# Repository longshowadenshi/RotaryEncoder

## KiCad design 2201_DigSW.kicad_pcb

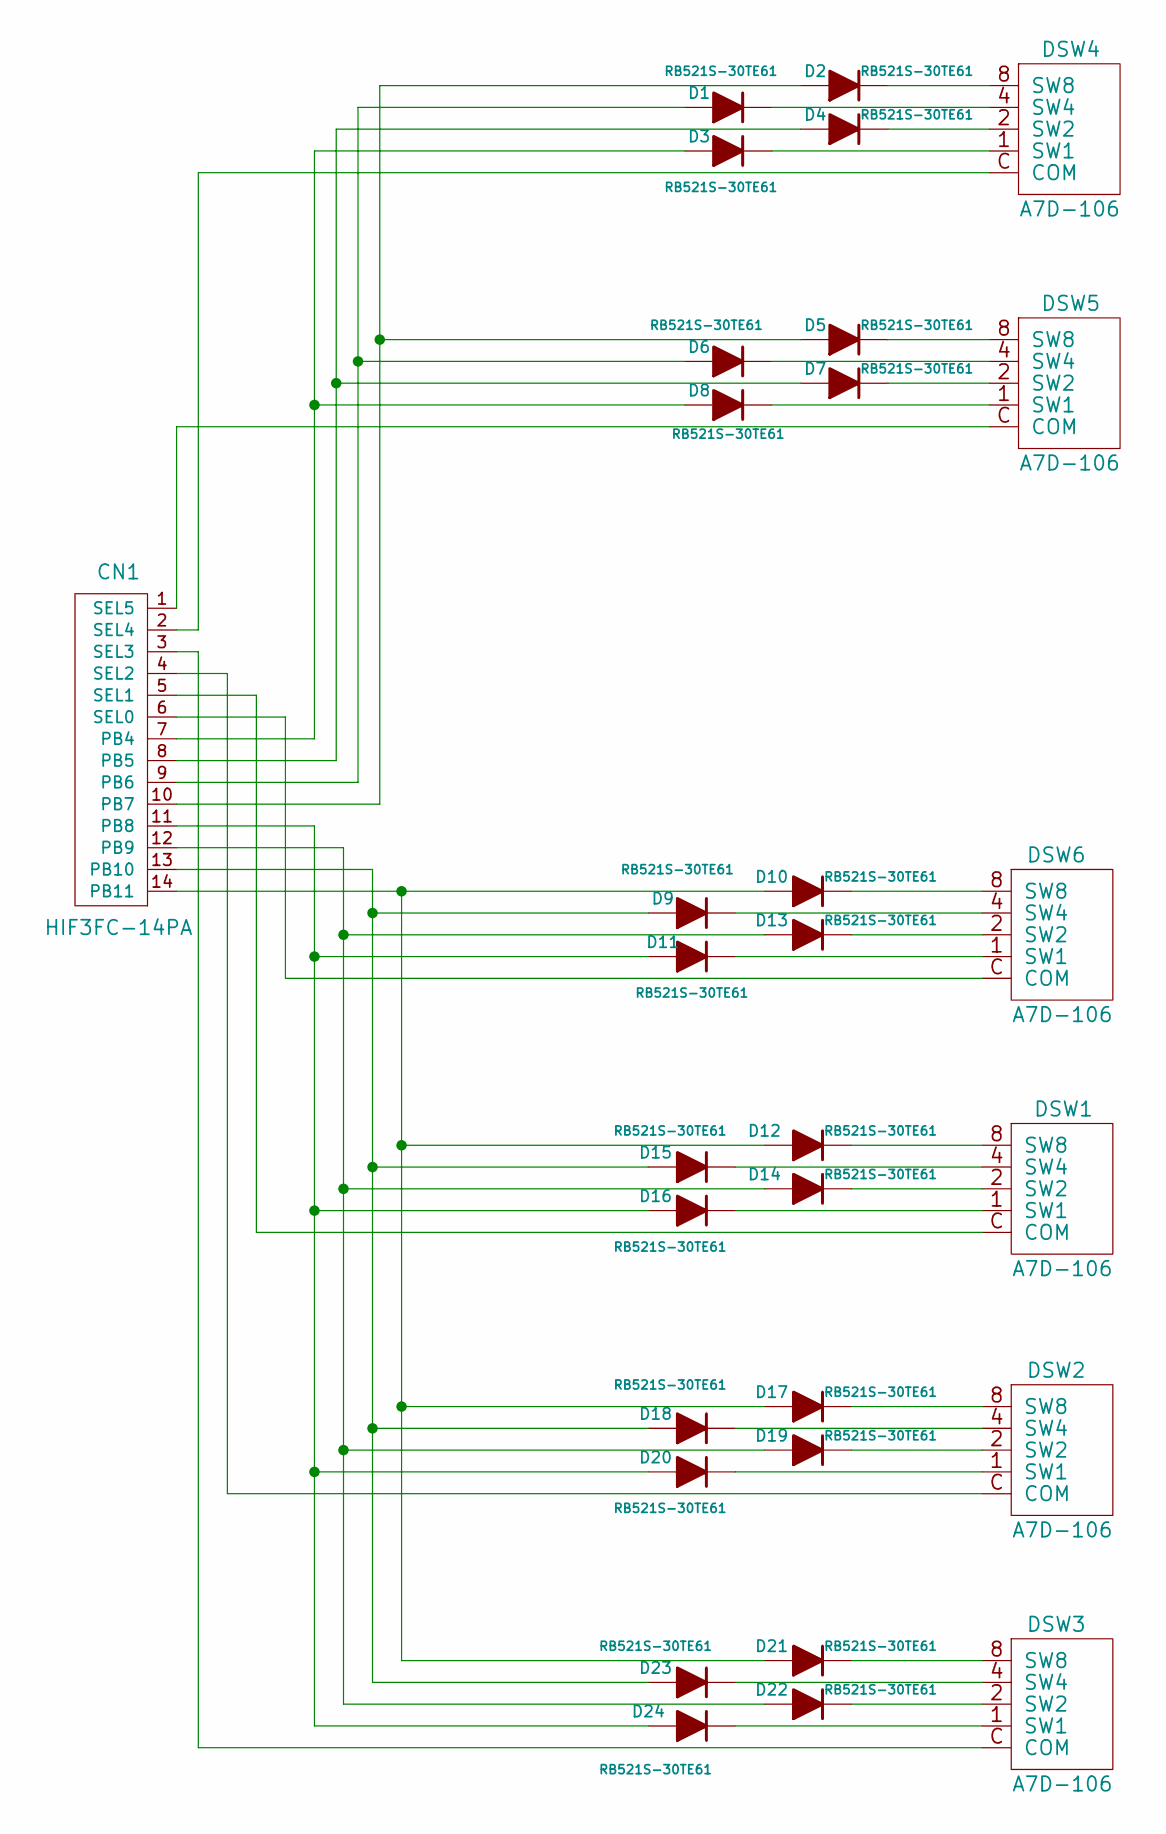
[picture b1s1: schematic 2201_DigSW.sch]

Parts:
CN1: HIF3FC-14PA; HIF3FC
D1, D2, D3, D4, D5, D6, D7, D8, D9, D10, D11, D12, D13, D14, D15, D16, D17, D18, D19, D20, D21, D22, D23, D24: RB521S-30TE61; 1SS355
DSW1, DSW3, DSW5: A7D-106; A7D-106-R
DSW2, DSW4, DSW6: A7D-106; A7D-106-L

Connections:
unnamed: CN1.1 (SEL5), DSW5.C (COM)
unnamed: CN1.2 (SEL4), DSW4.C (COM)
unnamed: CN1.3 (SEL3), DSW3.C (COM)
unnamed: CN1.4 (SEL2), DSW2.C (COM)
unnamed: CN1.5 (SEL1), DSW1.C (COM)
unnamed: CN1.6 (SEL0), DSW6.C (COM)
unnamed: CN1.7 (PB4), D3.1, D8.1
unnamed: CN1.8 (PB5), D4.1, D7.1
unnamed: CN1.9 (PB6), D1.1, D6.1
unnamed: CN1.10 (PB7), D2.1, D5.1
unnamed: CN1.11 (PB8), D11.1, D16.1, D20.1, D24.1
unnamed: CN1.12 (PB9), D13.1, D14.1, D19.1, D22.1
unnamed: CN1.13 (PB10), D9.1, D15.1, D18.1, D23.1
unnamed: CN1.14 (PB11), D10.1, D12.1, D17.1, D21.1
unnamed: D1.2, DSW4.4 (SW4)
unnamed: D2.2, DSW4.8 (SW8)
unnamed: D3.2, DSW4.1 (SW1)
unnamed: D4.2, DSW4.2 (SW2)
unnamed: D5.2, DSW5.8 (SW8)
unnamed: D6.2, DSW5.4 (SW4)
unnamed: D7.2, DSW5.2 (SW2)
unnamed: D8.2, DSW5.1 (SW1)
unnamed: D9.2, DSW6.4 (SW4)
unnamed: D10.2, DSW6.8 (SW8)
unnamed: D11.2, DSW6.1 (SW1)
unnamed: D12.2, DSW1.8 (SW8)
unnamed: D13.2, DSW6.2 (SW2)
unnamed: D14.2, DSW1.2 (SW2)
unnamed: D15.2, DSW1.4 (SW4)
unnamed: D16.2, DSW1.1 (SW1)
unnamed: D17.2, DSW2.8 (SW8)
unnamed: D18.2, DSW2.4 (SW4)
unnamed: D19.2, DSW2.2 (SW2)
unnamed: D20.2, DSW2.1 (SW1)
unnamed: D21.2, DSW3.8 (SW8)
unnamed: D22.2, DSW3.2 (SW2)
unnamed: D23.2, DSW3.4 (SW4)
unnamed: D24.2, DSW3.1 (SW1)

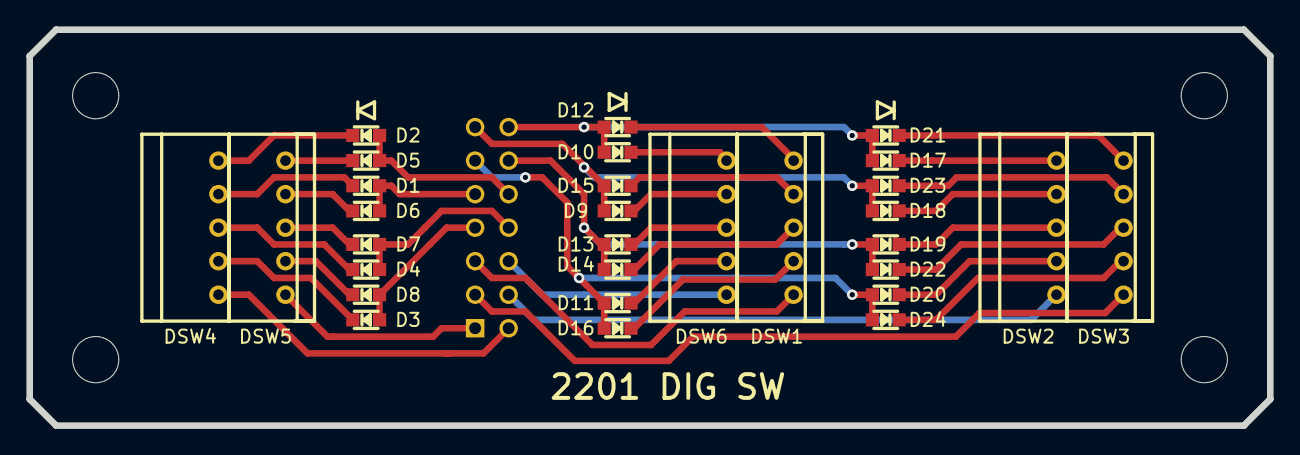
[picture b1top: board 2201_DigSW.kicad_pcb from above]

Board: 2 copper layers, 94.0 x 30.0 mm, 31 parts (1 on the bottom side), 38 nets.
